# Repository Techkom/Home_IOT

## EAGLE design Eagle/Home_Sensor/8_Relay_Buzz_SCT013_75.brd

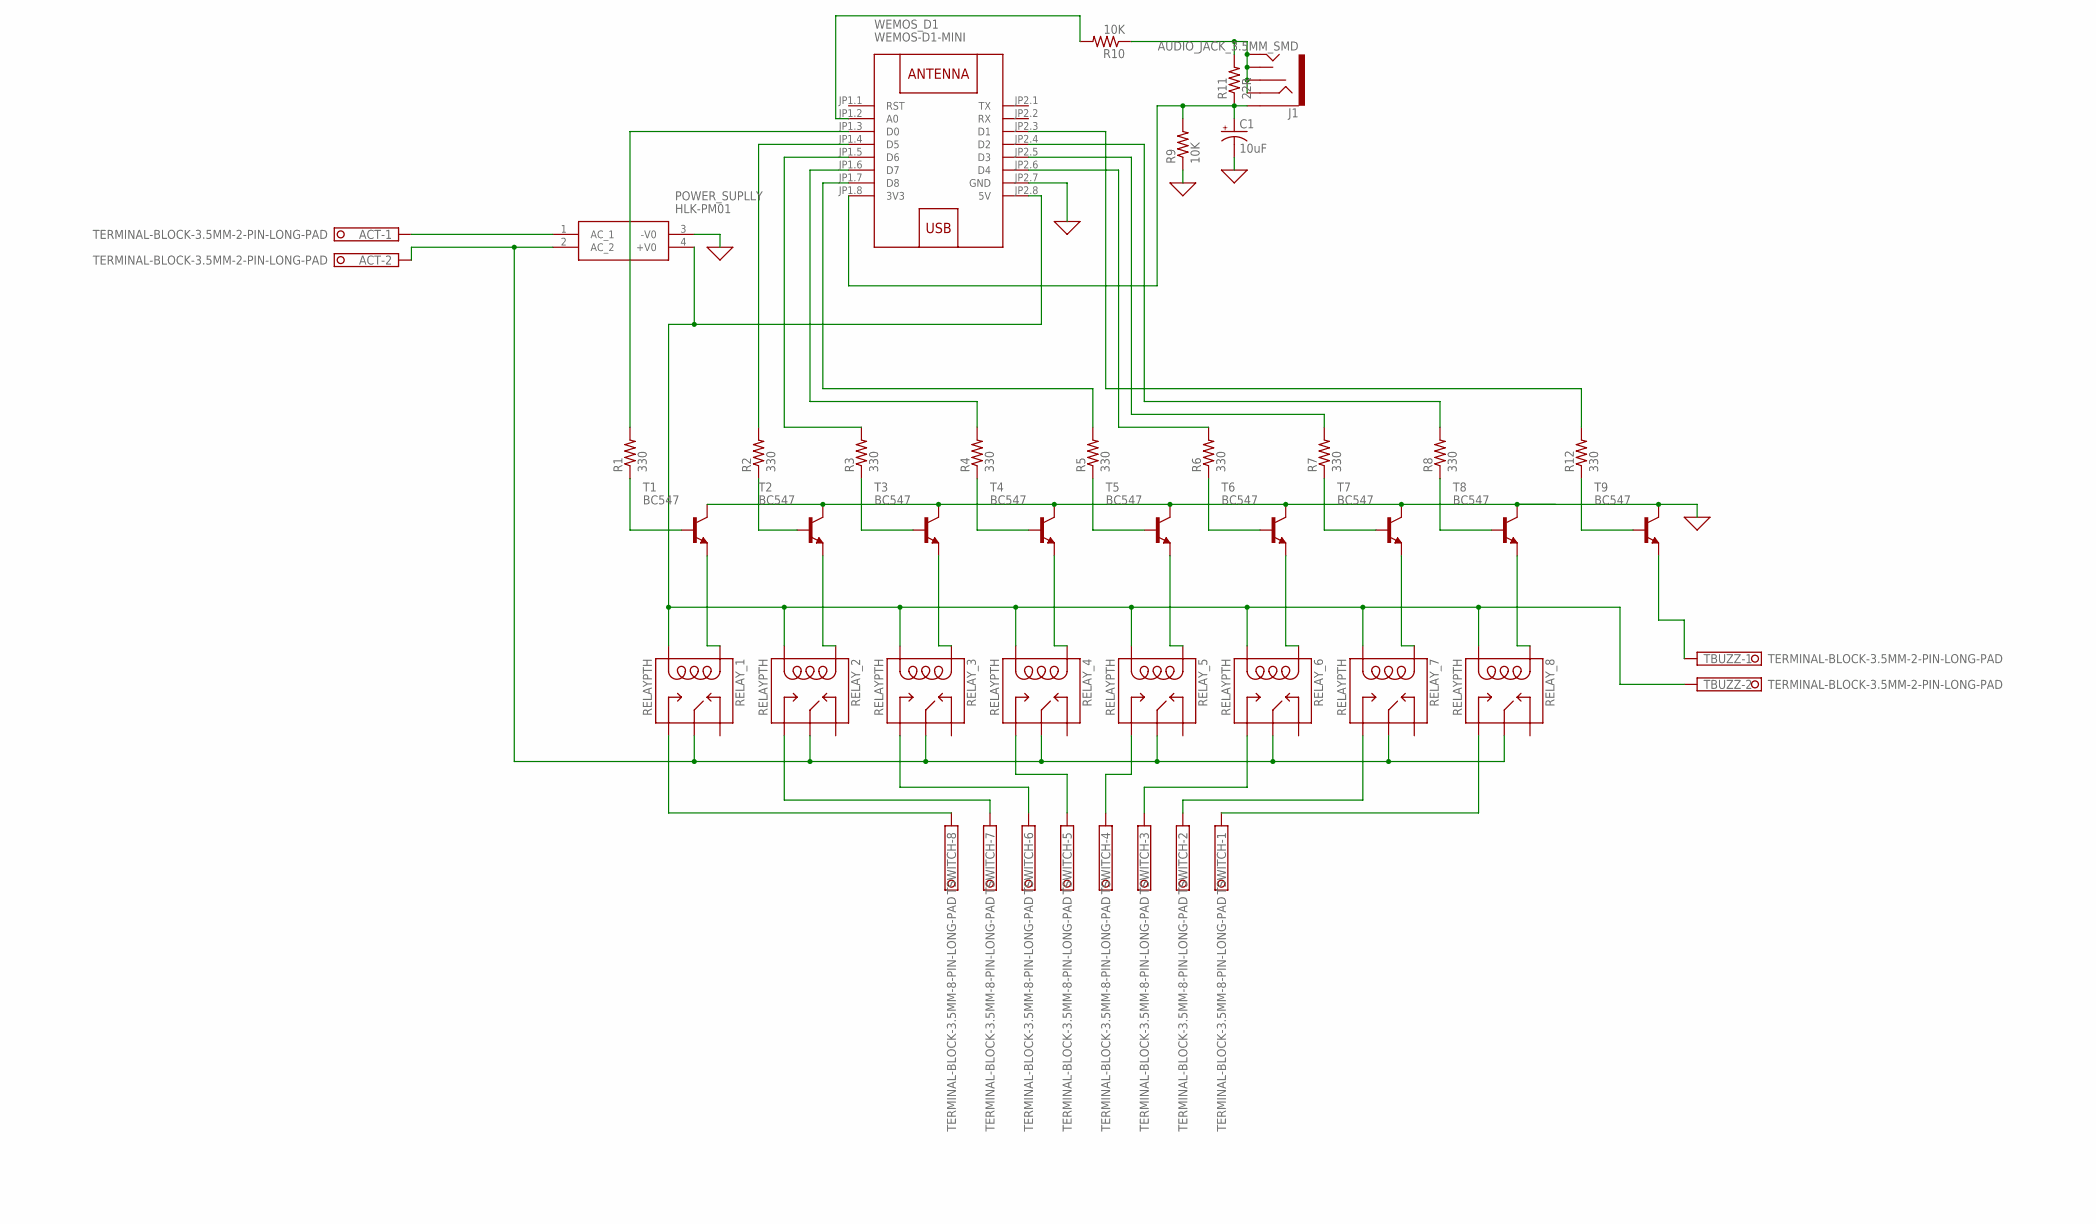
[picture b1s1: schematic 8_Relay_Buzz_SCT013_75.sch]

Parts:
ACT: TERMINAL-BLOCK-3.5MM-2-PIN-LONG-PAD; TERMINAL-BLOCK-2-PIN-3.5MM-LONG-PAD
C1: 10uF; E3,5-8
J1: AUDIO_JACK_3.5MM_SMD; AUDIO-JACK-3.5MM-SMD
POWER_SUPLLY: HLK-PM01; HLKPM01
R1, R2, R3, R4, R5, R6, R7, R8, R12: 330; 0207/5V
R9, R10: 10K; 0207/5V
R11: 22R; 0207/5V
RELAY_1, RELAY_2, RELAY_3, RELAY_4, RELAY_5, RELAY_6, RELAY_7, RELAY_8: RELAYPTH; SRD-05VDC-SL-C
T1, T2, T3, T4, T5, T6, T7, T8, T9: BC547; TO92
TBUZZ: TERMINAL-BLOCK-3.5MM-2-PIN-LONG-PAD; TERMINAL-BLOCK-2-PIN-3.5MM-LONG-PAD
TSWITCH: TERMINAL-BLOCK-3.5MM-8-PIN-LONG-PAD; TERMINAL-BLOCK-8-PIN-3.5MM-LONG-PAD
WEMOS_D1: WEMOS-D1-MINI

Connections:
0: C1.-, POWER_SUPLLY.3 (-V0), R9.1, T1.3 (C), T2.3 (C), T3.3 (C), T4.3 (C), T5.3 (C), T6.3 (C), T7.3 (C), T8.3 (C), T9.3 (C), WEMOS_D1.JP2.7 (GND)
3V: C1.+, J1.SLEEVE, R9.2, R11.1, WEMOS_D1.JP1.8 (3V3)
5V: POWER_SUPLLY.4 (+V0), RELAY_1.COIL0, RELAY_2.COIL0, RELAY_3.COIL0, RELAY_4.COIL0, RELAY_5.COIL0, RELAY_6.COIL0, RELAY_7.COIL0, RELAY_8.COIL0, TBUZZ.2, WEMOS_D1.JP2.8 (5V)
A0: R10.2, WEMOS_D1.JP1.2 (A0)
AC+: ACT.2, POWER_SUPLLY.2 (AC_2), RELAY_1.SWCOMMON, RELAY_2.SWCOMMON, RELAY_3.SWCOMMON, RELAY_4.SWCOMMON, RELAY_5.SWCOMMON, RELAY_6.SWCOMMON, RELAY_7.SWCOMMON, RELAY_8.SWCOMMON
AC-: ACT.1, POWER_SUPLLY.1 (AC_1)
BBZ: R12.1, T9.2 (B)
BR1: R1.1, T1.2 (B)
BR2: R2.1, T2.2 (B)
BR3: R3.1, T3.2 (B)
BR4: R4.1, T4.2 (B)
BR5: R5.1, T5.2 (B)
BR6: R6.1, T6.2 (B)
BR7: R7.1, T7.2 (B)
BR8: R8.1, T8.2 (B)
D0: R1.2, WEMOS_D1.JP1.3 (D0)
D1: R12.2, WEMOS_D1.JP2.3 (D1)
D2: R8.2, WEMOS_D1.JP2.4 (D2)
D3: R7.2, WEMOS_D1.JP2.5 (D3)
D4: R6.2, WEMOS_D1.JP2.6 (D4)
D5: R2.2, WEMOS_D1.JP1.4 (D5)
D6: R3.2, WEMOS_D1.JP1.5 (D6)
D7: R4.2, WEMOS_D1.JP1.6 (D7)
D8: R5.2, WEMOS_D1.JP1.7 (D8)
EBZ: T9.1 (E), TBUZZ.1
ER1: RELAY_1.COIL1, T1.1 (E)
ER2: RELAY_2.COIL1, T2.1 (E)
ER3: RELAY_3.COIL1, T3.1 (E)
ER4: RELAY_4.COIL1, T4.1 (E)
ER5: RELAY_5.COIL1, T5.1 (E)
ER6: RELAY_6.COIL1, T6.1 (E)
ER7: RELAY_7.COIL1, T7.1 (E)
ER8: RELAY_8.COIL1, T8.1 (E)
SA0: J1.RING, J1.RSH, J1.TIP, J1.TSH, R10.1, R11.2
SR1: RELAY_1.SWOPEN, TSWITCH.8
SR2: RELAY_2.SWOPEN, TSWITCH.7
SR3: RELAY_3.SWOPEN, TSWITCH.6
SR4: RELAY_4.SWOPEN, TSWITCH.5
SR5: RELAY_5.SWOPEN, TSWITCH.4
SR6: RELAY_6.SWOPEN, TSWITCH.3
SR7: RELAY_7.SWOPEN, TSWITCH.2
SR8: RELAY_8.SWOPEN, TSWITCH.1

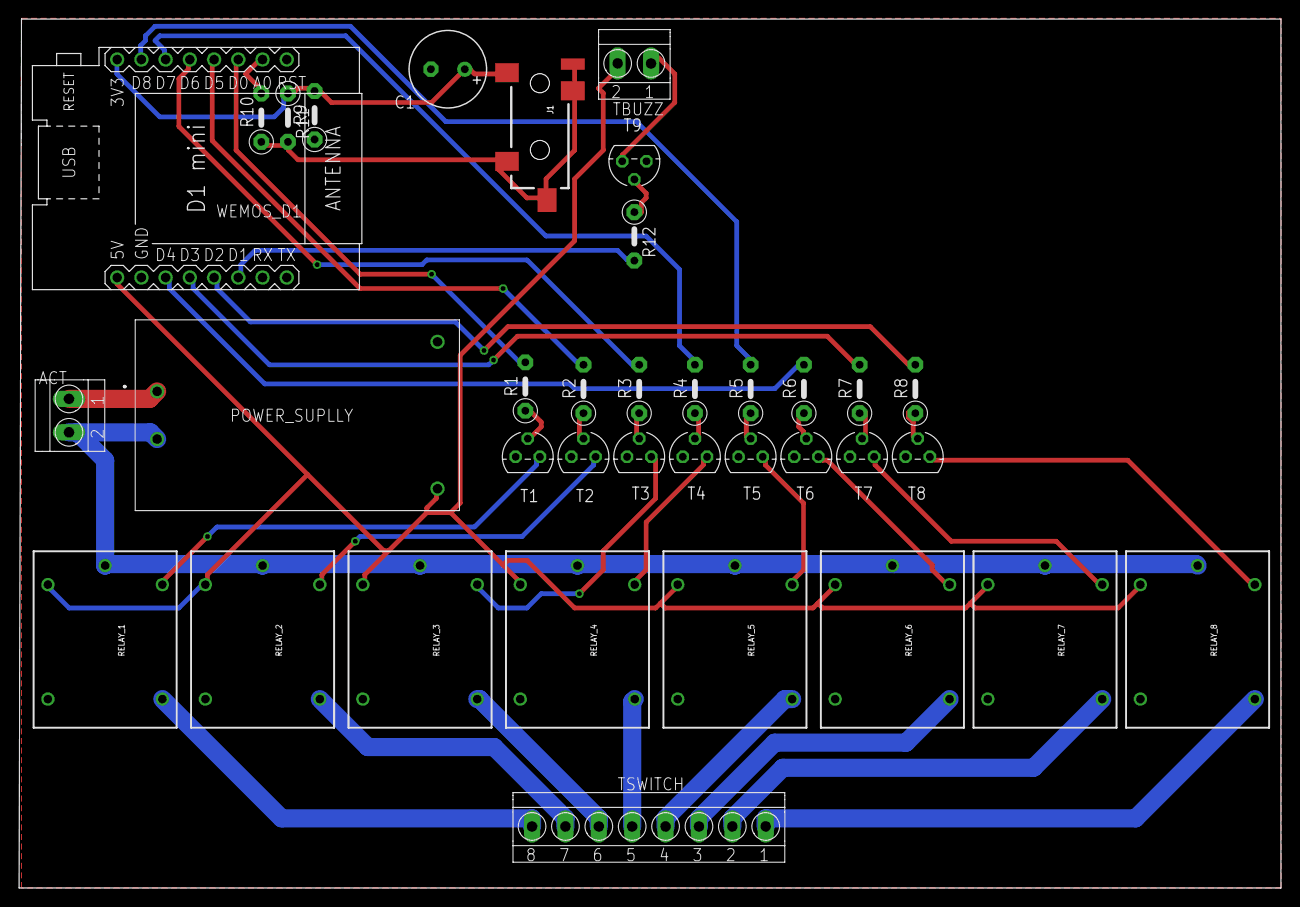
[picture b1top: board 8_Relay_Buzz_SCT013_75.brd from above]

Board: 2 copper layers, 132.3 x 91.1 mm, 36 parts (0 on the bottom side), 42 nets.

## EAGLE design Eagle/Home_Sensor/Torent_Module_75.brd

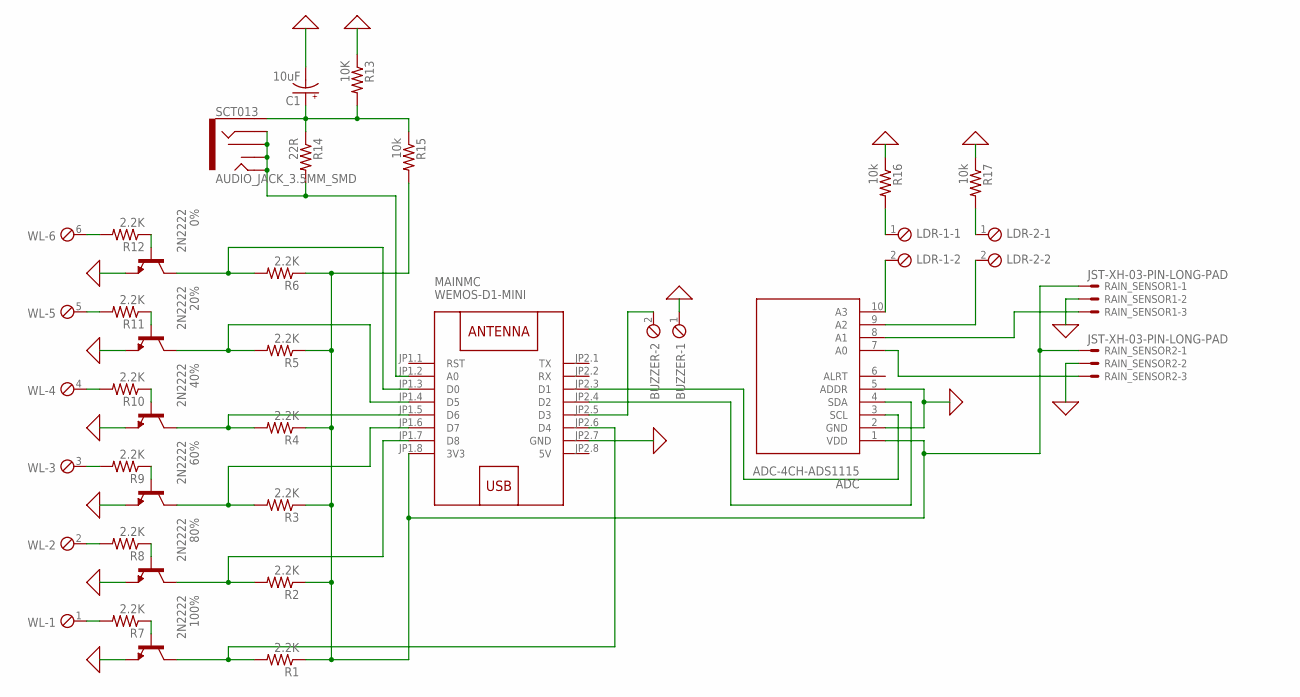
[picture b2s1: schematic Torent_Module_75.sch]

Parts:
0%, 20%, 40%, 60%, 80%, 100%: 2N2222; TO92-EBC-OVAL
ADC: ADC-4CH-ADS1115
BUZZER: MPT2; 2POL254
C1: 10uF; TT2D7
LDR-1, LDR-2: MPT2; 2POL254
MAINMC: WEMOS-D1-MINI
R1, R2, R3, R4, R5, R6, R7, R8, R9, R10, R11, R12: 2.2K; 0207/9
R13: 10K; 0207/9
R14: 22R; 0207/9
R15, R16, R17: 10k; 0207/9
RAIN_SENSOR1, RAIN_SENSOR2: JST-XH-03-PIN-LONG-PAD; JST-XH-03-PACKAGE-LONG-PAD
SCT013: AUDIO_JACK_3.5MM_SMD; AUDIO-JACK-3.5MM-SMD
WL: MPT6; 6POL254

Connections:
0: 0%.E, 20%.E, 40%.E, 60%.E, 80%.E, 100%.E, ADC.2 (GND), ADC.5 (ADDR), BUZZER.1, C1.-, MAINMC.JP2.7 (GND), R13.1, R16.1, R17.1, RAIN_SENSOR1.2, RAIN_SENSOR2.2
0%-1: 0%.B, R12.1
0%-2: R12.2, WL.6
3.3V: ADC.1 (VDD), MAINMC.JP1.8 (3V3), R1.1, R2.1, R3.1, R4.1, R5.1, R6.1, R15.2, RAIN_SENSOR1.1, RAIN_SENSOR2.1
5V: MAINMC.JP2.8 (5V)
20%-1: 20%.B, R11.1
20%-2: R11.2, WL.5
40%-1: 40%.B, R10.1
40%-2: R10.2, WL.4
60%-1: 60%.B, R9.1
60%-2: R9.2, WL.3
80%-1: 80%.B, R8.1
80%-2: R8.2, WL.2
100%-1: 100%.B, R7.1
100%-2: R7.2, WL.1
A0: MAINMC.JP1.2 (A0), R14.2, SCT013.RING, SCT013.RSH, SCT013.TIP, SCT013.TSH
ADSA2-0: ADC.9 (A2), LDR-2.2
ADSA2-1: LDR-2.1, R17.2
ADSA3-0: ADC.10 (A3), LDR-1.2
ADSA3-1: LDR-1.1, R16.2
D0: 0%.C, MAINMC.JP1.3 (D0), R6.2
D3: BUZZER.2, MAINMC.JP2.5 (D3)
D4: 100%.C, MAINMC.JP2.6 (D4), R1.2
D5: 20%.C, MAINMC.JP1.4 (D5), R5.2
D6: 40%.C, MAINMC.JP1.5 (D6), R4.2
D7: 60%.C, MAINMC.JP1.6 (D7), R3.2
D8: 80%.C, MAINMC.JP1.7 (D8), R2.2
unnamed: ADC.7 (A0), RAIN_SENSOR2.3
unnamed: ADC.8 (A1), RAIN_SENSOR1.3
SCL: ADC.3 (SCL), MAINMC.JP2.3 (D1)
SDA: ADC.4 (SDA), MAINMC.JP2.4 (D2)
VCC_STC013: C1.+, R13.2, R14.1, R15.1, SCT013.SLEEVE

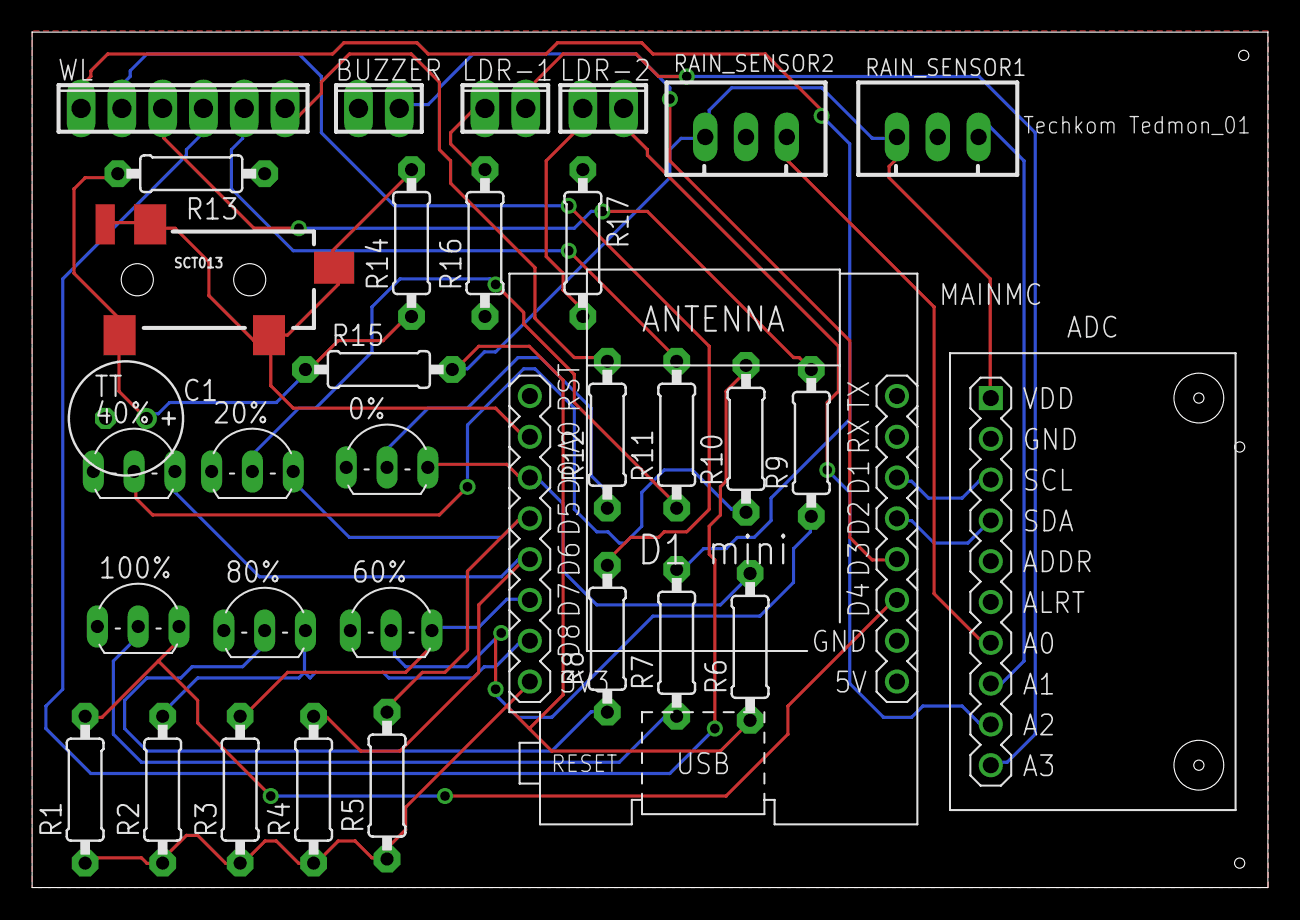
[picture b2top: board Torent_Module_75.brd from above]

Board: 2 copper layers, 76.9 x 53.3 mm, 33 parts (0 on the bottom side), 31 nets.

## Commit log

2020-11-07 finish ultrasonic read
2020-11-07 finish wifi
2021-01-04 20210103
2021-01-04 add Eagle File

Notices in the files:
parts and their libraries:
SparkFun-Connectors: Licensing: Creative Commons ShareAlike 4.0 International - https://creativecommons.org/licenses/by-sa/4.0
diy-modules: Released under the Creative Commons Attribution 4.0 International License: http://creativecommons.org/licenses/by/4.0
